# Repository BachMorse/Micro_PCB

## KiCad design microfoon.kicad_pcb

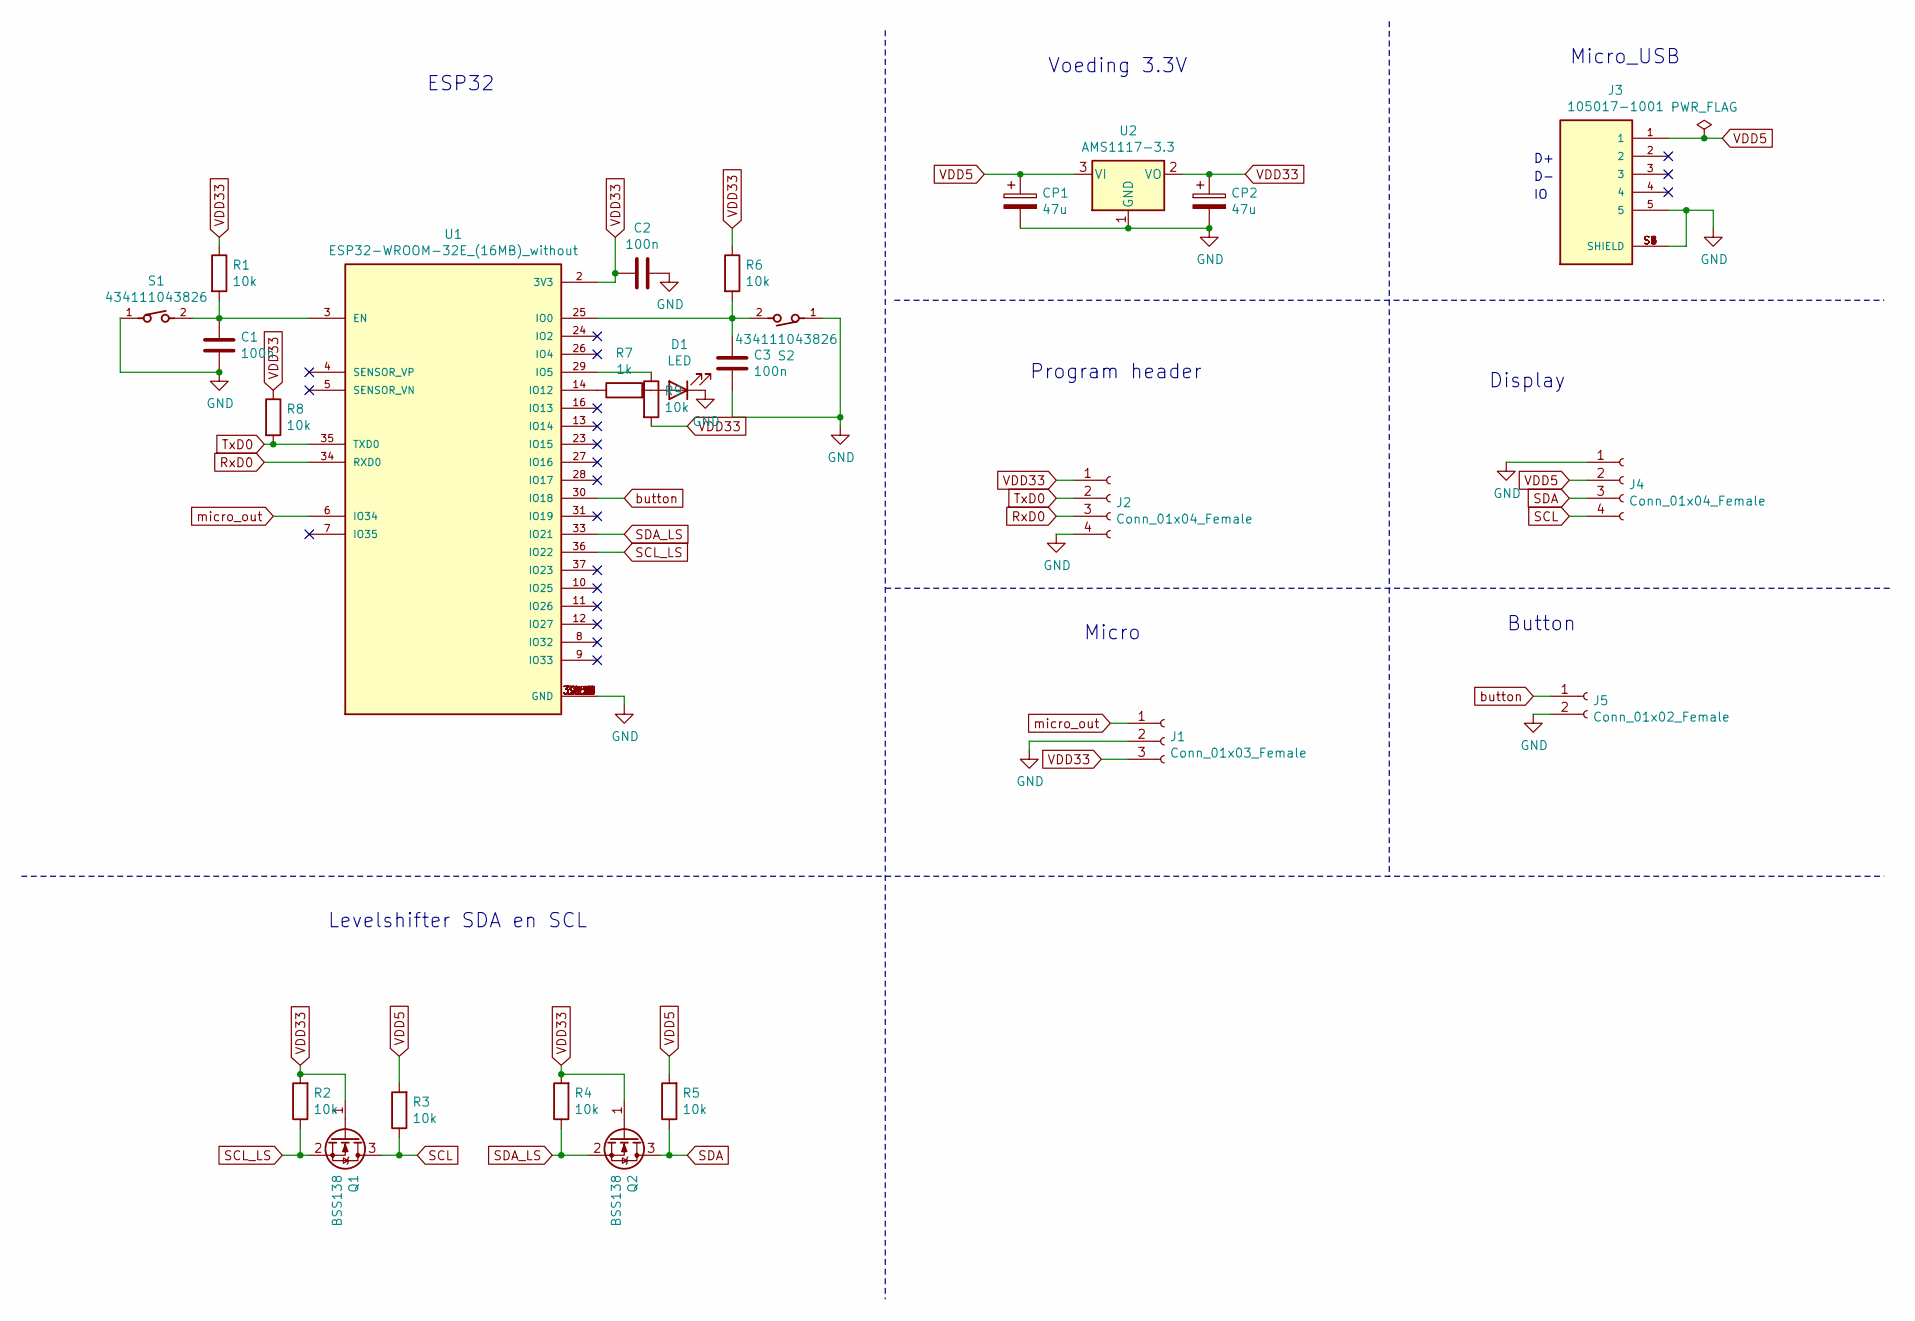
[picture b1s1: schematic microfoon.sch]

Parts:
C1, C2, C3: 100n; C_1206_3216Metric
CP1, CP2: 47u; CP_Elec_8x6.2
D1: LED; LED_1206_3216Metric
J1: Conn_01x03_Female; PinSocket_1x03_P2.54mm_Vertical
J2, J4: Conn_01x04_Female; PinSocket_1x04_P2.54mm_Vertical
J3: 105017-1001; MOLEX_105017-1001
J5: Conn_01x02_Female; PinSocket_1x02_P2.54mm_Vertical
Q1, Q2: BSS138; SOT-23
R1, R2, R3, R4, R5, R6, R8, R9: 10k; R_1206_3216Metric
R7: 1k; R_1206_3216Metric
S1, S2: 434111043826
U1: ESP32-WROOM-32E_(16MB)_without; MODULE_ESP32-WROOM-32E_(16MB)
U2: AMS1117-3.3; SOT-223-3_TabPin2

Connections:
GND: C1.2, C2.1, C3.2, CP1.2, CP2.2, D1.1 (K), J1.2, J2.4, J3.5, J3.S1 (SHIELD), J3.S2 (SHIELD), J3.S3 (SHIELD), J3.S4 (SHIELD), J3.S5 (SHIELD), J3.S6 (SHIELD), J4.1, J5.2, S1.1, S2.1, U1.1 (GND), U1.15 (GND), U1.38 (GND), U1.39_1 (GND), U1.39_2 (GND), U1.39_3 (GND), U1.39_4 (GND), U1.39_5 (GND), U1.39_6 (GND), U1.39_7 (GND), U1.39_8 (GND), U1.39_9 (GND), U1.39_10 (GND), U1.39_11 (GND), U1.39_12 (GND), U1.39_13 (GND), U1.39_14 (GND), U1.39_15 (GND), U1.39_16 (GND), U1.39_17 (GND), U1.39_18 (GND), U1.39_19 (GND), U1.39_20 (GND), U1.39_21 (GND), U2.1 (GND)
unnamed: C1.1, R1.2, S1.2, U1.3 (EN)
unnamed: C3.1, R6.2, S2.2, U1.25 (IO0)
unnamed: D1.2 (A), R7.2
unnamed: R7.1, U1.14 (IO12)
unnamed: R9.1, U1.29 (IO5)
RxD0: J2.3, U1.34 (RXD0)
SCL: J4.4, Q1.3 (D), R3.1
SCL_LS: Q1.2 (S), R2.1, U1.36 (IO22)
SDA: J4.3, Q2.3 (D), R5.1
SDA_LS: Q2.2 (S), R4.1, U1.33 (IO21)
TxD0: J2.2, R8.2, U1.35 (TXD0)
VDD5: CP1.1, J3.1, J4.2, R3.2, R5.2, U2.3 (VI)
VDD33: C2.2, CP2.1, J1.3, J2.1, Q1.1 (G), Q2.1 (G), R1.1, R2.2, R4.2, R6.1, R8.1, R9.2, U1.2 (3V3), U2.2 (VO)
button: J5.1, U1.30 (IO18)
micro_out: J1.1, U1.6 (IO34)

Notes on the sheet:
Voeding 3.3V
ESP32
Micro_USB
Program header
Display
Micro
Button
Levelshifter SDA en SCL

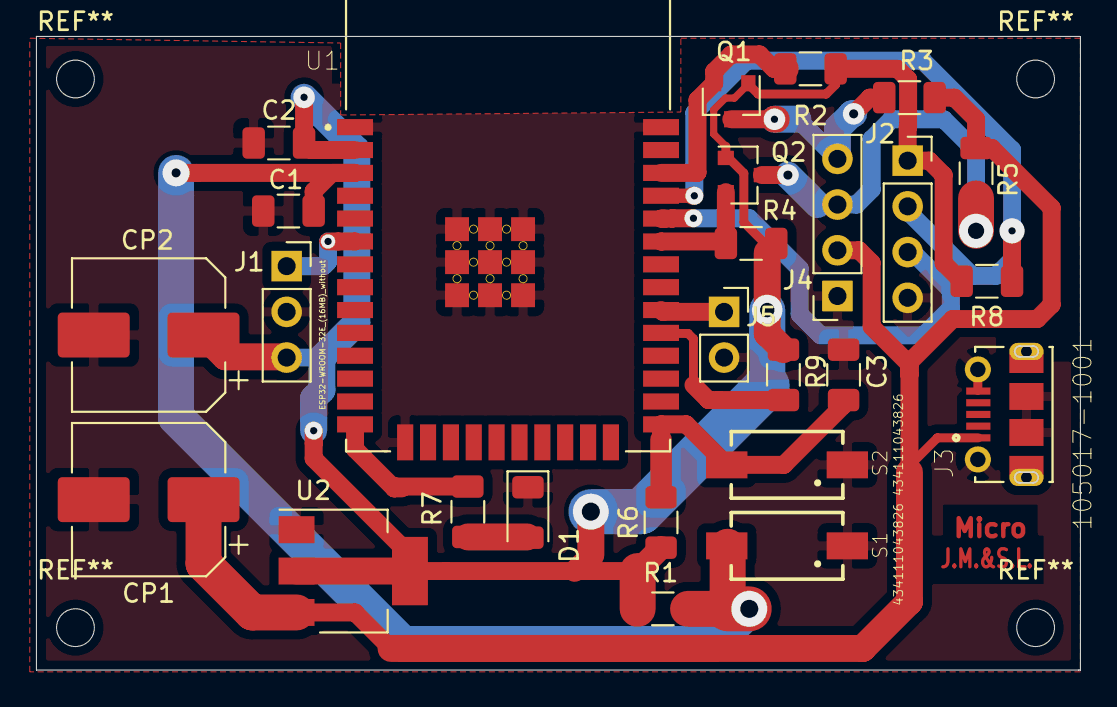
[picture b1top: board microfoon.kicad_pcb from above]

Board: 2 copper layers, 58.0 x 35.2 mm, 26 parts (0 on the bottom side), 16 nets.

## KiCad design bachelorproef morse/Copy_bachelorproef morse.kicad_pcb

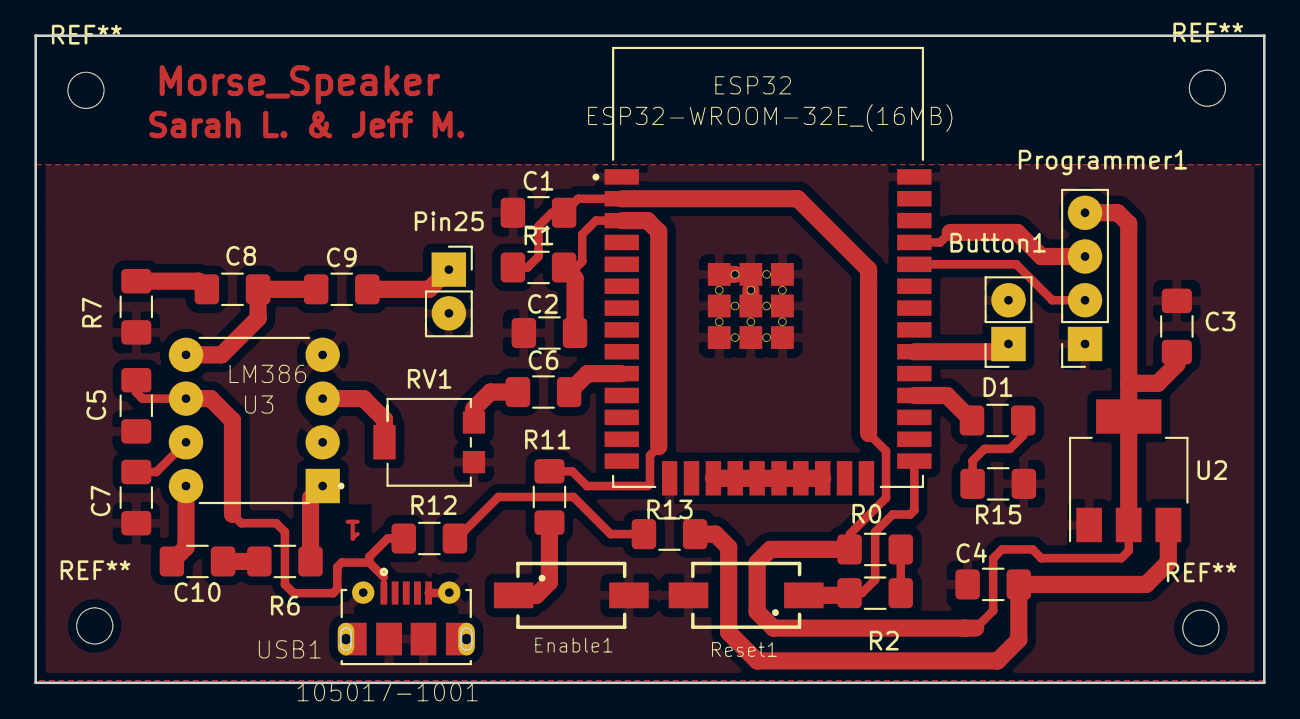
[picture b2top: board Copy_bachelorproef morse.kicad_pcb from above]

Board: 2 copper layers, 71.4 x 37.6 mm, 30 parts (0 on the bottom side), 25 nets.

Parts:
Button1: Conn_01x02_Female; PinSocket_1x02_P2.54mm_Vertical
C1, C2: 100n; C_1206_3216Metric_Pad1.42x1.75mm_HandSolder
C3: 10u; C_1206_3216Metric_Pad1.42x1.75mm_HandSolder
C4: 100u; C_1206_3216Metric_Pad1.42x1.75mm_HandSolder
C5, C8: 0.1uF; C_1206_3216Metric_Pad1.42x1.75mm_HandSolder
C6, C7, C10: 10uF; C_1206_3216Metric_Pad1.42x1.75mm_HandSolder
C9: 220uF; C_1206_3216Metric_Pad1.42x1.75mm_HandSolder
D1: LED; R_1206_3216Metric_Pad1.42x1.75mm_HandSolder
ESP32: ESP32-WROOM-32E_(16MB); MODULE_ESP32-WROOM-32E_(16MB)
Enable1: 434111043826
Pin25: Conn_01x02_Female; PinSocket_1x02_P2.54mm_Vertical
Programmer1: Conn_01x04_Female; PinSocket_1x04_P2.54mm_Vertical
R0, R11, R12, R13: 0; R_1206_3216Metric_Pad1.42x1.75mm_HandSolder
R1, R2: 10k; R_1206_3216Metric_Pad1.42x1.75mm_HandSolder
R6: 1.2k; R_1206_3216Metric_Pad1.42x1.75mm_HandSolder
R7: 10; R_1206_3216Metric_Pad1.42x1.75mm_HandSolder
R15: 2.7k; R_1206_3216Metric_Pad1.42x1.75mm_HandSolder
RV1: 10k; Potentiometer_Bourns_3224G_Horizontal
Reset1: 0; 434111043826
U2: AMS1117-3.3; SOT-223-3_TabPin2
U3: LM386; DIP794W45P254L959H508Q8
USB1: 105017-1001; MOLEX_105017-1001

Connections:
GND: Button1.2, C1.1, C2.2, C3.2, C4.2, C5.2, C7.2, ESP32.1, ESP32.15, ESP32.38, ESP32.39_1, ESP32.39_2, ESP32.39_3, ESP32.39_4, ESP32.39_5, ESP32.39_6, ESP32.39_7, ESP32.39_8, ESP32.39_9, ESP32.39_10, ESP32.39_11, ESP32.39_12, ESP32.39_13, ESP32.39_14, ESP32.39_15, ESP32.39_16, ESP32.39_17, ESP32.39_18, ESP32.39_19, ESP32.39_20, ESP32.39_21, Enable1.2, Pin25.2, Programmer1.1, R7.2, R15.1, RV1.3, Reset1.2, U2.1, U3.2, U3.4, USB1.5, USB1.S1, USB1.S2, USB1.S3, USB1.S4, USB1.S5, USB1.S6
I|O: C6.2, ESP32.10
unnamed: Button1.1, ESP32.30
unnamed: C2.1, ESP32.3, R1.2, R11.1
unnamed: C6.1, RV1.1
unnamed: C7.1, U3.7
unnamed: C8.1, C9.1, U3.5
unnamed: C8.2, R7.1
unnamed: C9.2, Pin25.1
unnamed: C10.1, R6.2
unnamed: C10.2, U3.8
unnamed: D1.1, R15.2
unnamed: D1.2, ESP32.28
unnamed: ESP32.17, ESP32.18, ESP32.19, ESP32.20, ESP32.21, ESP32.22
unnamed: ESP32.25, R2.2, Reset1.1
unnamed: ESP32.34, Programmer1.2
unnamed: ESP32.35, Programmer1.3
unnamed: Enable1.1, R11.2
unnamed: R0.2, R2.1
unnamed: R6.1, U3.1
unnamed: R12.1, R13.2
unnamed: RV1.2, U3.3
V5: C4.1, R13.1, U2.3
V5_direct: C5.1, R12.2, U3.6, USB1.1
Vdd: C1.2, C3.1, ESP32.2, Programmer1.4, R0.1, R1.1, U2.2

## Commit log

2021-05-09 kleine aanpassingen achteraf
